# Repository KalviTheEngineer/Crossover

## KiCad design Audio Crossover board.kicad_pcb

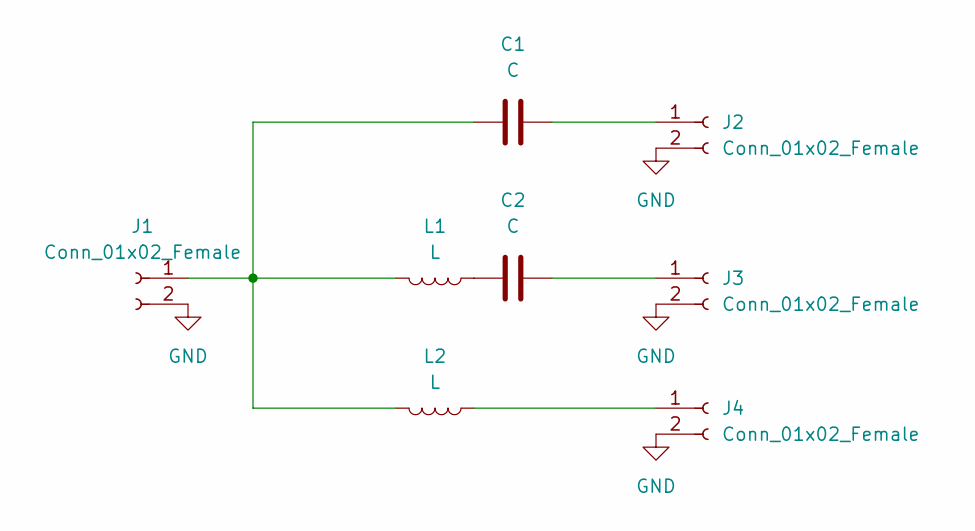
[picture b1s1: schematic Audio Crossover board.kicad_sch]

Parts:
C1: C; Jamicon 10uF 63V Audio Crossover Capacitor
C2: C; M.D.L. 100uF 100V Audio Crossover Capacitor
J1, J2, J3, J4: Conn_01x02_Female; Pad do lutowania audio przewodów
L1: L; Jantzen Audio000-1989 0,47mH 0,36Ohm
L2: L; Jantzen Audio 000-2169 3,3mH 0,7Ohm

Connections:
GND: J1.2, J2.2, J3.2, J4.2
unnamed: C1.2, J2.1
unnamed: C2.2, J3.1
unnamed: J4.1, L2.1
unnamed: C2.1, L1.1
unnamed: C1.1, J1.1, L1.2, L2.2

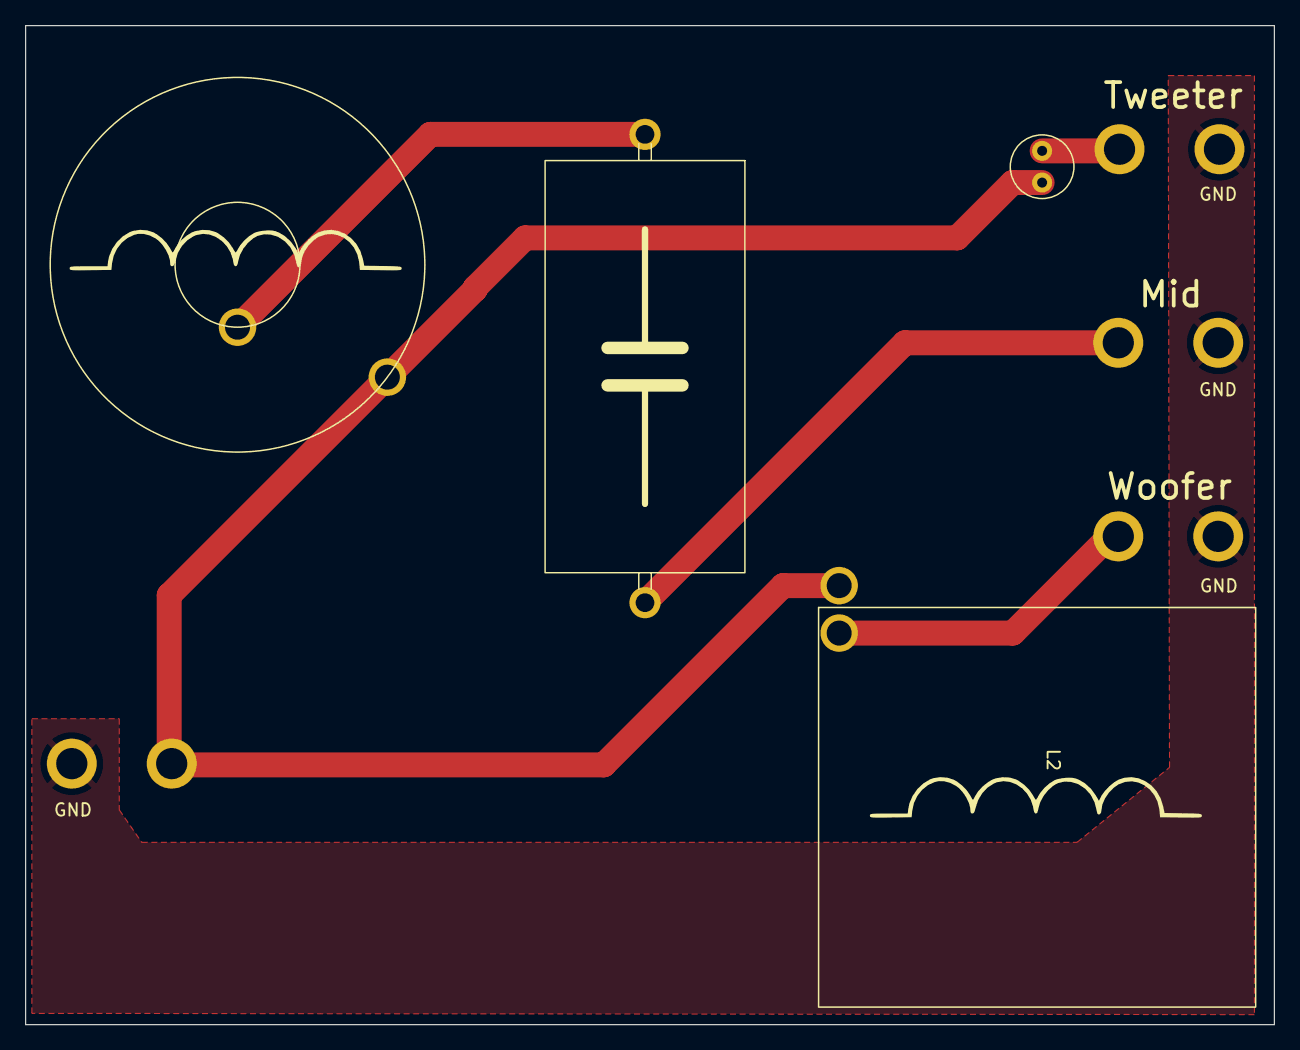
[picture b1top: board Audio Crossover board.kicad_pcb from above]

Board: 2 copper layers, 100.0 x 80.0 mm, 8 parts (0 on the bottom side), 6 nets.

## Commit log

2023-06-29 Gotowe PCB Folder do poprawy
